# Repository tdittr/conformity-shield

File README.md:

# Conformity Shield

This is a design for a Arduino Uno R3 compatible shield, that connects an RP2354B to all IO pins. It is inteded to be used to test implementations of [`embedded-hal`](https://docs.rs/embedded-hal/).

**Warning:** rev1 of this board has known problems, do not produce boards from this yet, see the issue tracker for details!

## License

This project is licensed under the [CERN-OHL-P license](LICENSE), except for the contents of [`ProjectSpecific.pretty`](ProjectSpecific.pretty) and [`Project_Specific.kicad_sym`](Project_Specific.kicad_sym) which are partially copied from the [RP235xB example](https://datasheets.raspberrypi.com/rp2350/hardware-design-with-rp2350.pdf) by Raspberry Pi.

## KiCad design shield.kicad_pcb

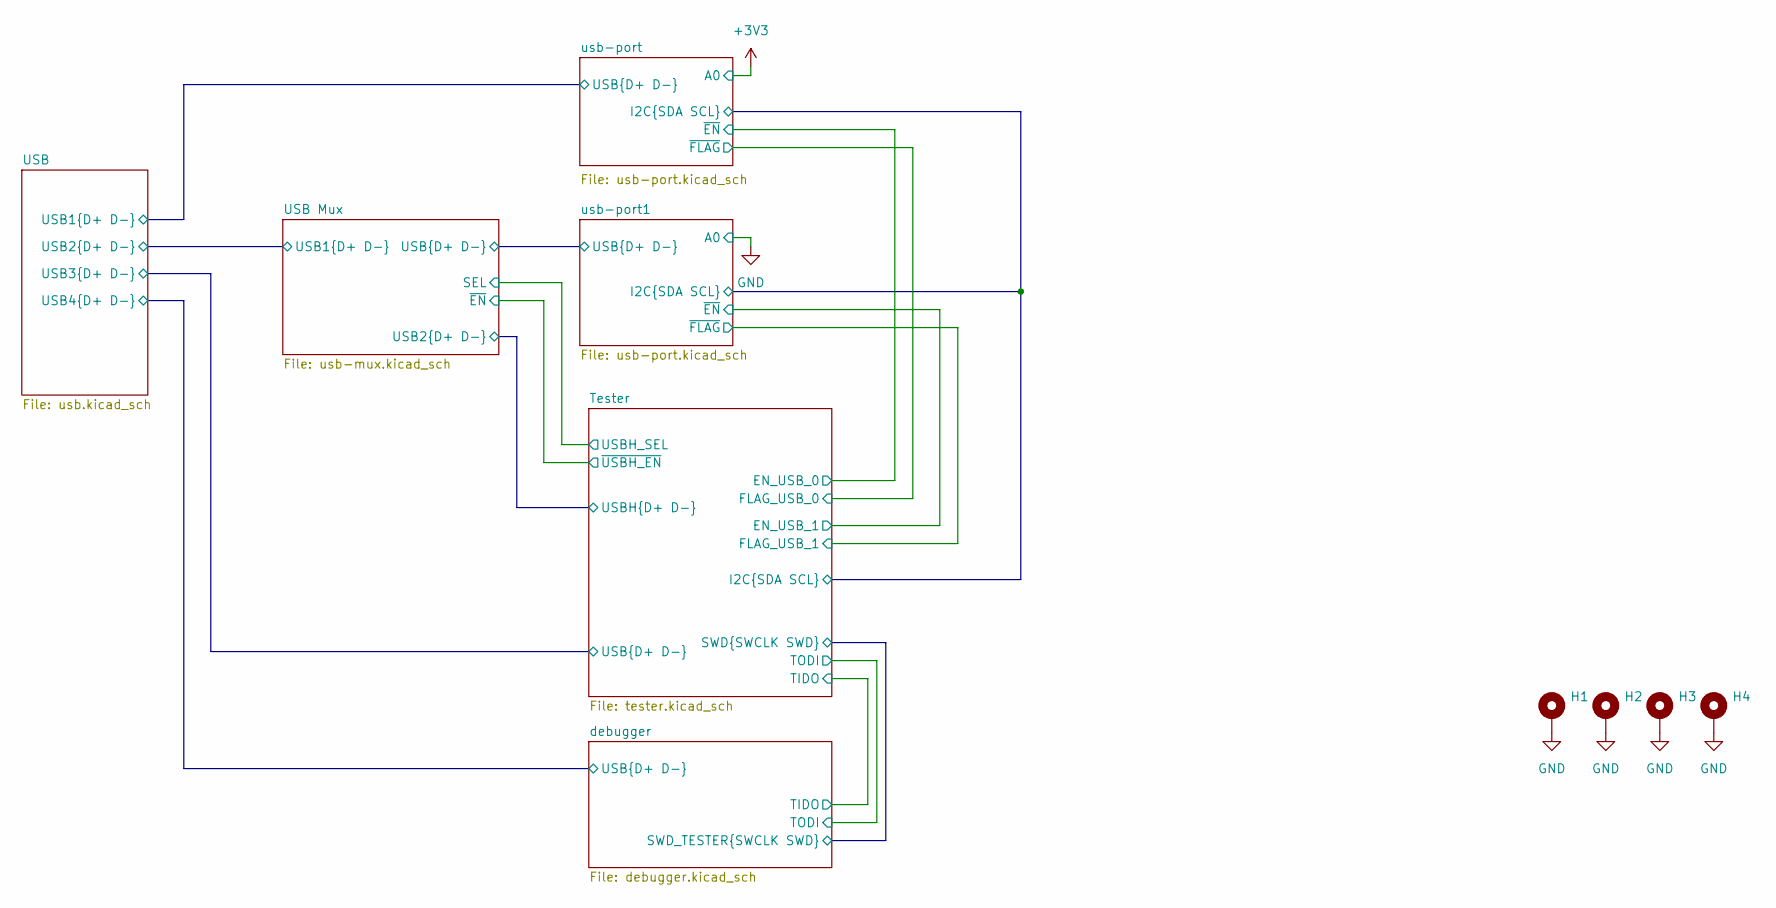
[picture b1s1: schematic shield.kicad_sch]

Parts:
H1, H2, H3, H4: MountingHole_Pad; MountingHole_2.5mm_Pad_Via

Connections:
GND: H1.1, H2.1, H3.1, H4.1; also elsewhere on the board

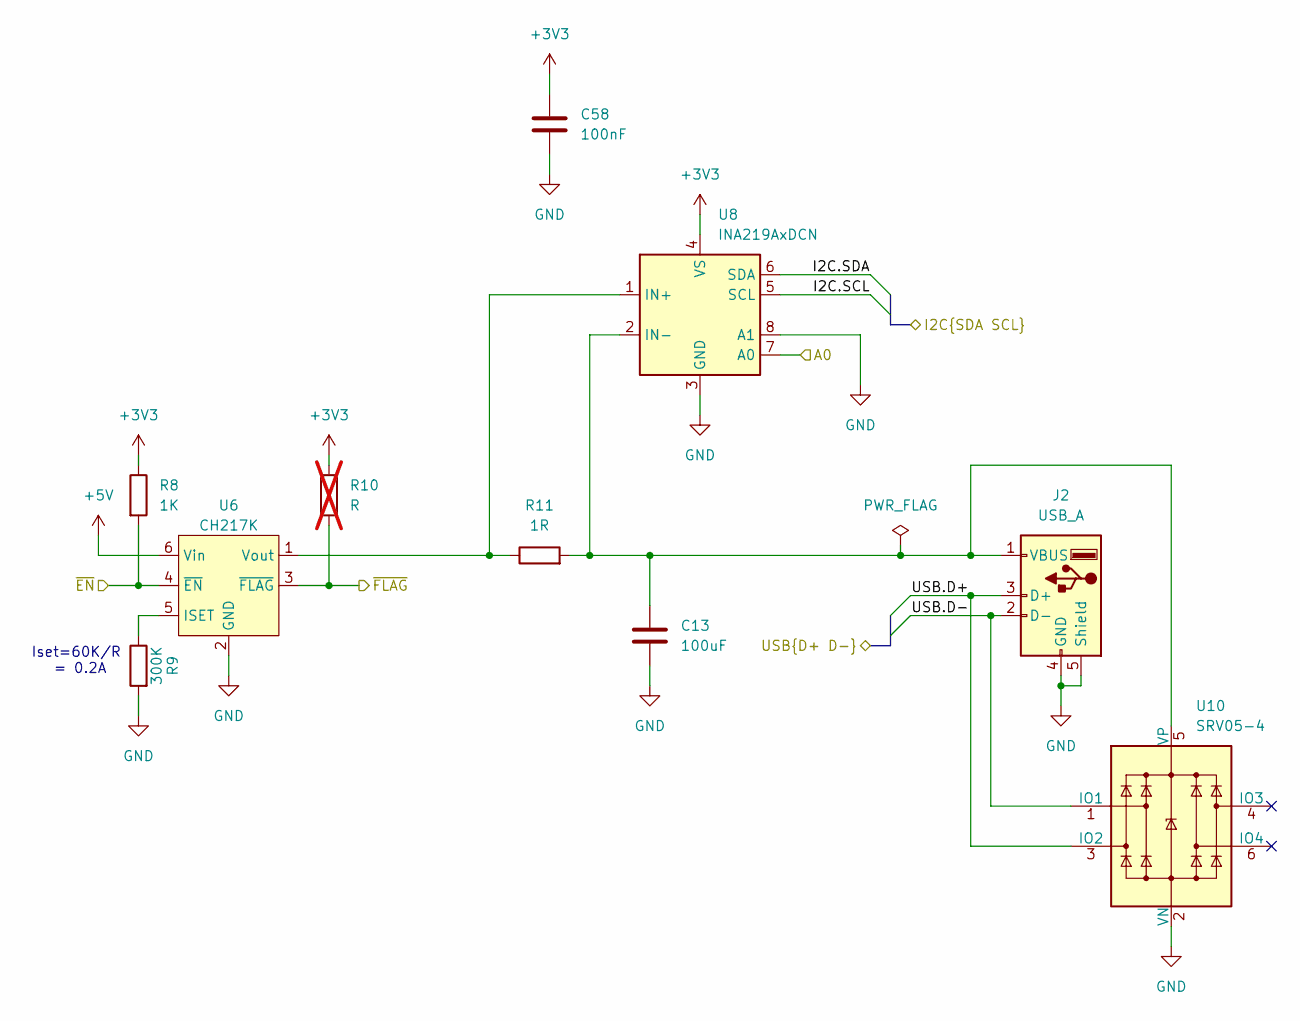
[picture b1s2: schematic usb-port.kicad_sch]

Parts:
C13: 100uF; C_1206_3216Metric; LCSC C15008
C58: 100nF; C_0402_1005Metric; LCSC C1525
J2: USB_A; USB_A_Receptacle_GCT_USB1046; LCSC C6307429
R8: 1K; R_0402_1005Metric; LCSC C11702
R9: 300K; R_0603_1608Metric; LCSC C23024
R10: R; R_0603_1608Metric_Pad0.98x0.95mm_HandSolder; not fitted
R11: 1R; R_0402_1005Metric; LCSC C25086
U6: CH217K; SOT-23-6; LCSC C7462749
U8: INA219AxDCN; SOT-23-8; LCSC C87469
U10: SRV05-4; SOT-23-6; LCSC C7420376

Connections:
+3V3: C58.1, R8.1, R10.1, U8.4 (VS), U8.7 (A0); also elsewhere on the board
+5V: U6.6 (Vin); also elsewhere on the board
/Tester/EN_USB_0: R8.2, U6.4 (~EN); also elsewhere on the board
/Tester/FLAG_USB_0: R10.2, U6.3 (~FLAG); also elsewhere on the board
/Tester/I2C.SCL: U8.5 (SCL); also elsewhere on the board
/Tester/I2C.SDA: U8.6 (SDA); also elsewhere on the board
/USB/USB1.D+: J2.3 (D+), U10.3 (IO2); also elsewhere on the board
/USB/USB1.D-: J2.2 (D-), U10.1 (IO1); also elsewhere on the board
GND: C13.2, C58.2, J2.4 (GND), J2.5 (Shield), R9.2, U6.2 (GND), U8.3 (GND), U8.8 (A1), U10.2 (VN); also elsewhere on the board
unnamed: C13.1, J2.1 (VBUS), R11.2, U8.2 (IN-), U10.5 (VP)
unnamed: R9.1, U6.5 (ISET)
unnamed: R11.1, U6.1 (Vout), U8.1 (IN+)

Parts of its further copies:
C52: 100uF; C_1206_3216Metric; LCSC C15008
C59: 100nF; C_0402_1005Metric; LCSC C1525
J3: USB_A; USB_A_Receptacle_GCT_USB1046; LCSC C6307429
R12: 1K; R_0402_1005Metric; LCSC C11702
R13: 300K; R_0603_1608Metric; LCSC C23024
R14: R; R_0603_1608Metric_Pad0.98x0.95mm_HandSolder; not fitted
R15: 1R; R_0402_1005Metric; LCSC C25086
U7: CH217K; SOT-23-6; LCSC C7462749
U9: INA219AxDCN; SOT-23-8; LCSC C87469
U11: SRV05-4; SOT-23-6; LCSC C7420376

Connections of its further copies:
+3V3: C59.1, R12.1, R14.1, U9.4 (VS); also elsewhere on the board
+5V: U7.6 (Vin); also elsewhere on the board
/Tester/EN_USB_1: R12.2, U7.4 (~EN); also elsewhere on the board
/Tester/FLAG_USB_1: R14.2, U7.3 (~FLAG); also elsewhere on the board
/Tester/I2C.SCL: U9.5 (SCL); also elsewhere on the board
/Tester/I2C.SDA: U9.6 (SDA); also elsewhere on the board
/USB Mux/USB.D+: J3.3 (D+), U11.3 (IO2); also elsewhere on the board
/USB Mux/USB.D-: J3.2 (D-), U11.1 (IO1); also elsewhere on the board
GND: C52.2, C59.2, J3.4 (GND), J3.5 (Shield), R13.2, U7.2 (GND), U9.3 (GND), U9.7 (A0), U9.8 (A1), U11.2 (VN); also elsewhere on the board
unnamed: C52.1, J3.1 (VBUS), R15.2, U9.2 (IN-), U11.5 (VP)
unnamed: R13.1, U7.5 (ISET)
unnamed: R15.1, U7.1 (Vout), U9.1 (IN+)

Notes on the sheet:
Iset=60K/R = 0.2A

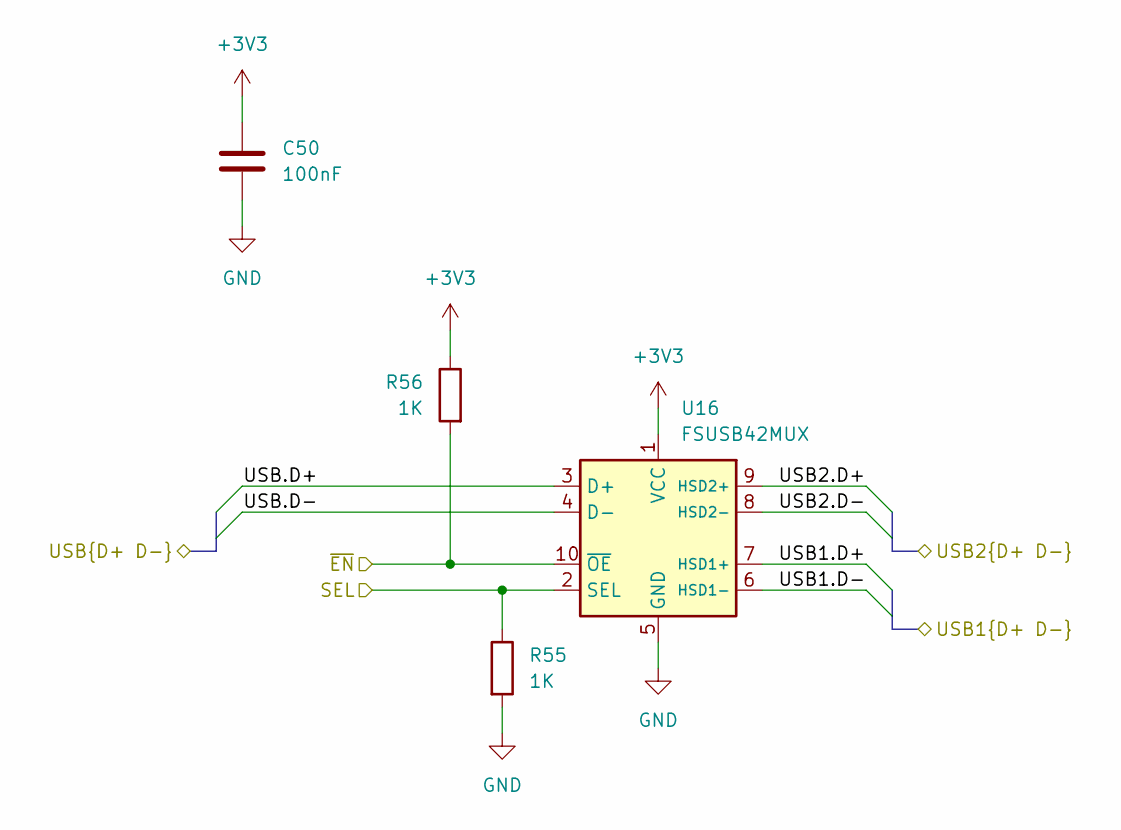
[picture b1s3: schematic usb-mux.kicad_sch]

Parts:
C50: 100nF; C_0402_1005Metric; LCSC C1525
R55, R56: 1K; R_0402_1005Metric; LCSC C11702
U16: FSUSB42MUX; MSOP-10_3x3mm_P0.5mm; LCSC C11355

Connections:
+3V3: C50.1, R56.1, U16.1 (VCC); also elsewhere on the board
/Tester/USBH.D+: U16.9 (HSD2+); also elsewhere on the board
/Tester/USBH.D-: U16.8 (HSD2-); also elsewhere on the board
/Tester/USBH_SEL: R55.1, U16.2 (SEL); also elsewhere on the board
/Tester/~USBH_EN: R56.2, U16.10 (~OE); also elsewhere on the board
/USB Mux/USB1.D+: U16.7 (HSD1+); also elsewhere on the board
/USB Mux/USB1.D-: U16.6 (HSD1-); also elsewhere on the board
/USB Mux/USB.D+: U16.3 (D+); also elsewhere on the board
/USB Mux/USB.D-: U16.4 (D-); also elsewhere on the board
GND: C50.2, R55.2, U16.5 (GND); also elsewhere on the board

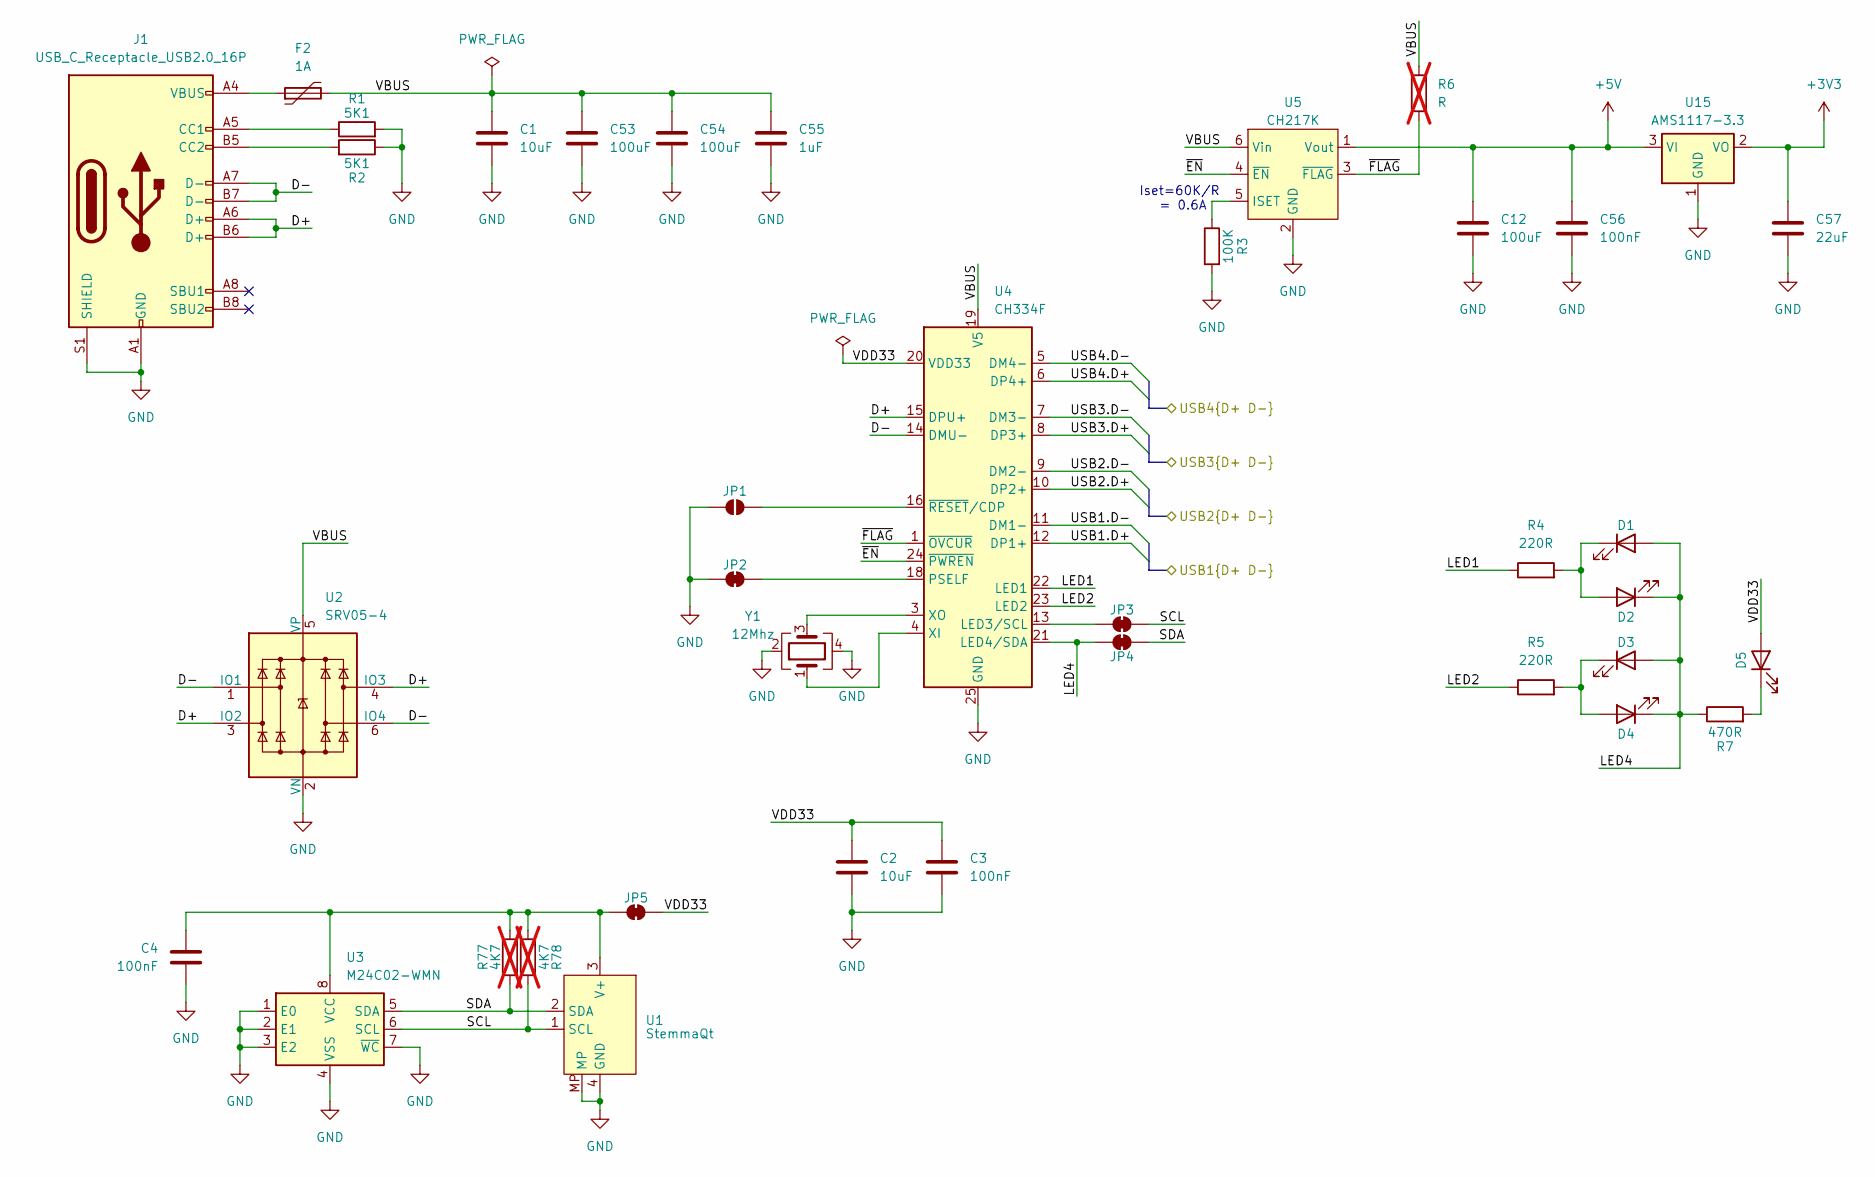
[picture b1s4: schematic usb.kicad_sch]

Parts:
C1, C2: 10uF; C_0402_1005Metric; LCSC C15525
C3, C4, C56: 100nF; C_0402_1005Metric; LCSC C1525
C12, C53, C54: 100uF; C_1206_3216Metric; LCSC C15008
C55: 1uF; C_0402_1005Metric; LCSC C52923
C57: 22uF; C_0805_2012Metric; LCSC C45783
D1, D2, D3, D4, D5: LED; LED_0805_2012Metric; LCSC C2297
F2: 1A; Fuse_1206_3216Metric_Pad1.42x1.75mm_HandSolder; LCSC C720075
J1: USB_C_Receptacle_USB2.0_16P; USB_C_Receptacle_G-Switch_GT-USB-7010ASV; LCSC C2988369
JP1: SolderJumper_2_Open; SolderJumper-2_P1.3mm_Open_RoundedPad1.0x1.5mm
JP2, JP3, JP4, JP5: SolderJumper_2_Bridged; SolderJumper-2_P1.3mm_Bridged_RoundedPad1.0x1.5mm
R1, R2: 5K1; R_0402_1005Metric; LCSC C25905
R3: 100K; R_0603_1608Metric; LCSC C23162
R4, R5: 220R; R_0402_1005Metric; LCSC C25091
R6: R; R_0603_1608Metric_Pad0.98x0.95mm_HandSolder; not fitted
R7: 470R; R_0402_1005Metric; LCSC C25117
R77, R78: 4K7; R_0402_1005Metric_Pad0.72x0.64mm_HandSolder; LCSC C25900; not fitted
U1: StemmaQt; JST_SH_SM04B-SRSS-TB_1x04-1MP_P1.00mm_Horizontal; LCSC C160404
U2: SRV05-4; SOT-23-6; LCSC C7420376
U3: M24C02-WMN; SOIC-8_3.9x4.9mm_P1.27mm; LCSC C7562
U4: CH334F; QFN-24-1EP_4x4mm_P0.5mm_EP2.7x2.7mm_ThermalVias; LCSC C5187527
U5: CH217K; SOT-23-6; LCSC C7462749
U15: AMS1117-3.3; SOT-223-3_TabPin2; LCSC C6186
Y1: 12Mhz; Crystal_SMD_3225-4Pin_3.2x2.5mm; LCSC C9002

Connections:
+3V3: C57.1, U15.2 (VO); also elsewhere on the board
+5V: C12.1, C56.1, U5.1 (Vout), U15.3 (VI); also elsewhere on the board
/Tester/USB.D+: U4.8 (DP3+); also elsewhere on the board
/Tester/USB.D-: U4.7 (DM3-); also elsewhere on the board
/USB Mux/USB1.D+: U4.10 (DP2+); also elsewhere on the board
/USB Mux/USB1.D-: U4.9 (DM2-); also elsewhere on the board
/USB/D+: J1.A6 (D+), J1.B6 (D+), U2.3 (IO2), U2.4 (IO3), U4.15 (DPU+)
/USB/D-: J1.A7 (D-), J1.B7 (D-), U2.1 (IO1), U2.6 (IO4), U4.14 (DMU-)
/USB/LED1: R4.1, U4.22 (LED1)
/USB/LED2: R5.1, U4.23 (LED2)
/USB/LED4: D1.2 (A), D2.1 (K), D3.2 (A), D4.1 (K), JP4.1 (A), R7.1, U4.21 (LED4/SDA)
/USB/SCL: JP3.2 (B), R78.1, U1.1 (SCL), U3.6 (SCL)
/USB/SDA: JP4.2 (B), R77.1, U1.2 (SDA), U3.5 (SDA)
/USB/USB1.D+: U4.12 (DP1+); also elsewhere on the board
/USB/USB1.D-: U4.11 (DM1-); also elsewhere on the board
/USB/USB4.D+: U4.6 (DP4+); also elsewhere on the board
/USB/USB4.D-: U4.5 (DM4-); also elsewhere on the board
/USB/VBUS: C1.1, C53.1, C54.1, C55.1, F2.2, R6.1, U2.5 (VP), U4.19 (V5), U5.6 (Vin)
/USB/VDD33: C2.1, C3.1, D5.2 (A), JP5.2 (B), U4.20 (VDD33)
/USB/~EN: U4.24 (~PWREN), U5.4 (~EN)
/USB/~FLAG: R6.2, U4.1 (~OVCUR), U5.3 (~FLAG)
GND: C1.2, C2.2, C3.2, C4.2, C12.2, C53.2, C54.2, C55.2, C56.2, C57.2, J1.A1 (GND), J1.A12 (GND), J1.B1 (GND), J1.B12 (GND), J1.S1 (SHIELD), JP1.1 (A), JP2.1 (A), R1.2, R2.1, R3.2, U1.4 (GND), U1.MP, U2.2 (VN), U3.1 (E0), U3.2 (E1), U3.3 (E2), U3.4 (VSS), U3.7 (~WC), U4.25 (GND), U5.2 (GND), U15.1 (GND), Y1.2, Y1.4; also elsewhere on the board
unnamed: D1.1 (K), D2.2 (A), R4.2
unnamed: D3.1 (K), D4.2 (A), R5.2
unnamed: D5.1 (K), R7.2
unnamed: F2.1, J1.A4 (VBUS), J1.A9 (VBUS), J1.B4 (VBUS), J1.B9 (VBUS)
unnamed: J1.A5 (CC1), R1.1
unnamed: J1.B5 (CC2), R2.2
unnamed: JP1.2 (B), U4.16 (~RESET/CDP)
unnamed: JP2.2 (B), U4.18 (PSELF)
unnamed: JP3.1 (A), U4.13 (LED3/SCL)
unnamed: C4.1, JP5.1 (A), R77.2, R78.2, U1.3 (V+), U3.8 (VCC)
unnamed: U4.4 (XI), Y1.1
unnamed: U4.3 (XO), Y1.3
unnamed: R3.1, U5.5 (ISET)

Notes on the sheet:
Iset=60K/R = 0.6A

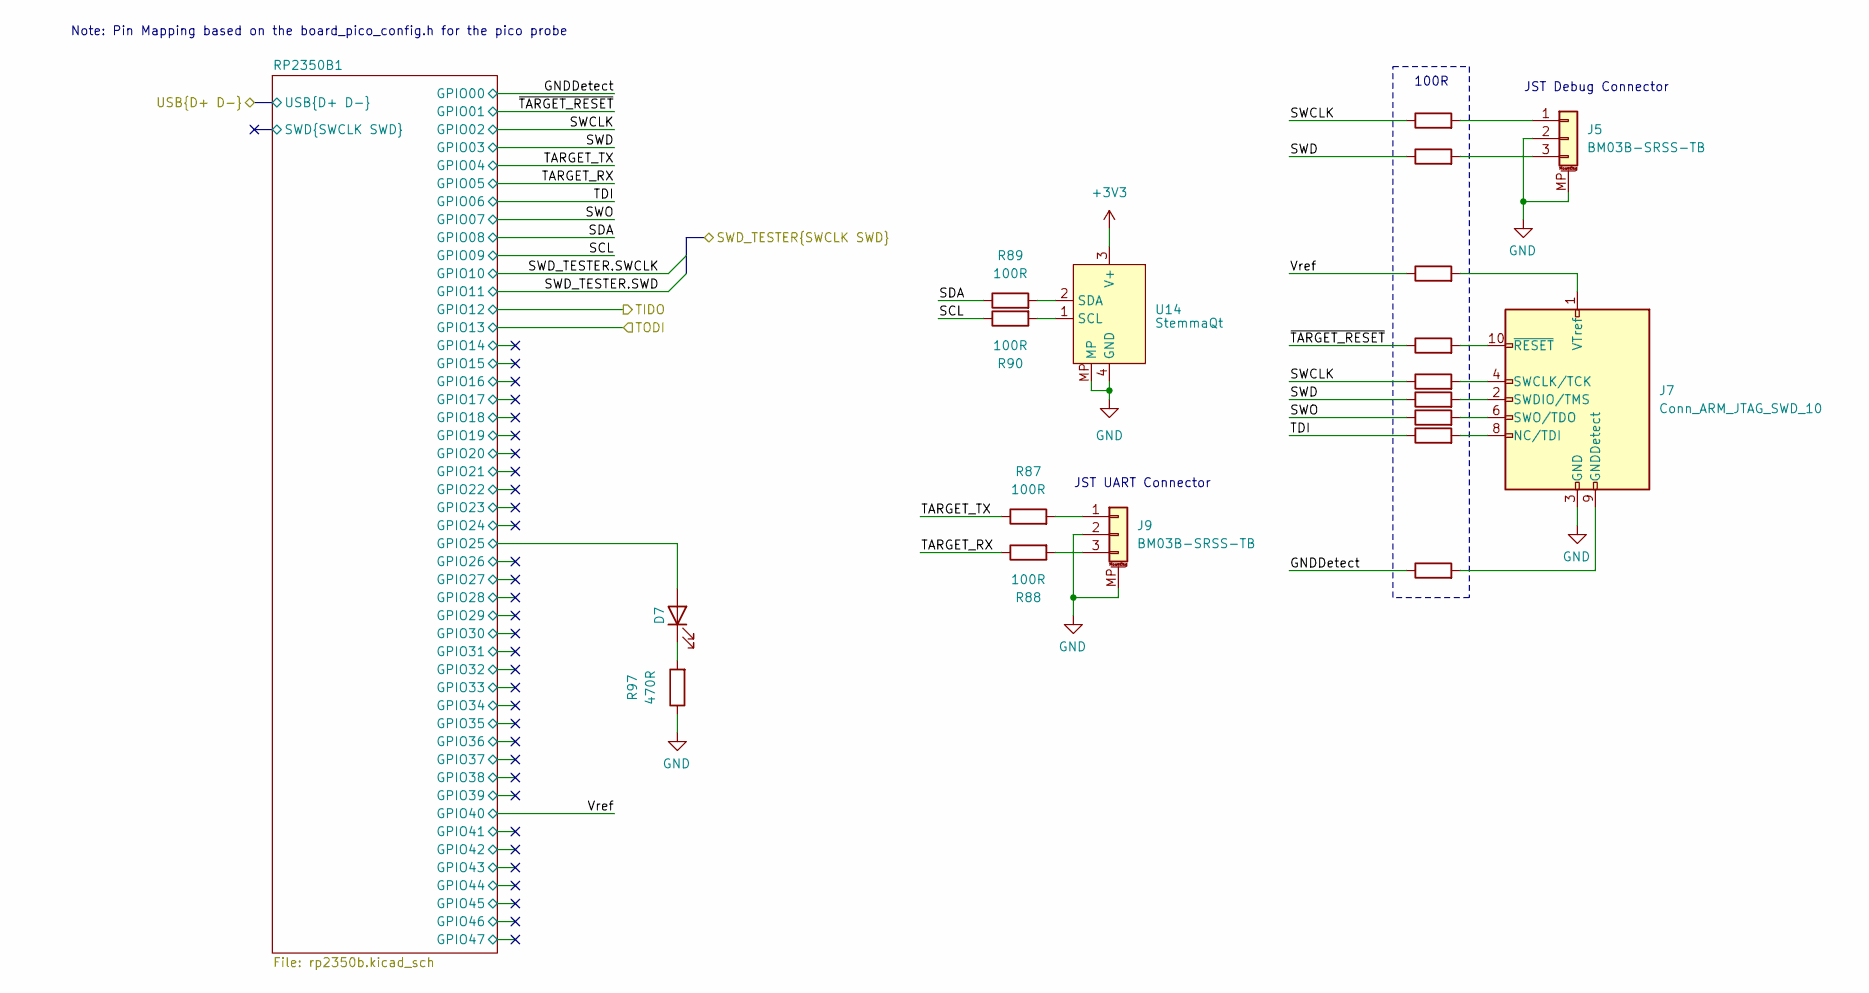
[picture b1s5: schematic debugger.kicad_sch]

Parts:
D7: LED; LED_0805_2012Metric; LCSC C2297
J5, J9: BM03B-SRSS-TB; JST_SH_BM03B-SRSS-TB_1x03-1MP_P1.00mm_Vertical; LCSC C160389
J7: Conn_ARM_JTAG_SWD_10; PinHeader_2x05_P1.27mm_Vertical_SMD_IDC; LCSC C42372555
R69, R70, R71, R72, R73, R74, R81, R85, R86, R87, R88, R89, R90: 100R; R_0402_1005Metric_Pad0.72x0.64mm_HandSolder; LCSC C25076
R97: 470R; R_0402_1005Metric_Pad0.72x0.64mm_HandSolder; LCSC C25117
U14: StemmaQt; JST_SH_SM04B-SRSS-TB_1x04-1MP_P1.00mm_Horizontal; LCSC C160404

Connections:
+3V3: U14.3 (V+); also elsewhere on the board
/debugger/GNDDetect: R81.1; also elsewhere on the board
/debugger/RP2350B1/GPIO25: D7.2 (A); also elsewhere on the board
/debugger/SCL: R90.1; also elsewhere on the board
/debugger/SDA: R89.1; also elsewhere on the board
/debugger/SWCLK: R71.1, R85.1; also elsewhere on the board
/debugger/SWD: R72.1, R86.1; also elsewhere on the board
/debugger/SWO: R73.1; also elsewhere on the board
/debugger/TARGET_RX: R88.1; also elsewhere on the board
/debugger/TARGET_TX: R87.1; also elsewhere on the board
/debugger/TDI: R74.1; also elsewhere on the board
/debugger/Vref: R69.1; also elsewhere on the board
/debugger/~TARGET_RESET: R70.1; also elsewhere on the board
GND: J5.2, J5.MP (MountPin), J7.3 (GND), J7.5 (GND), J9.2, J9.MP (MountPin), R97.1, U14.4 (GND), U14.MP; also elsewhere on the board
unnamed: D7.1 (K), R97.2
unnamed: J5.1, R85.2
unnamed: J5.3, R86.2
unnamed: J7.9 (GNDDetect), R81.2
unnamed: J7.8 (NC/TDI), R74.2
unnamed: J7.4 (SWCLK/TCK), R71.2
unnamed: J7.2 (SWDIO/TMS), R72.2
unnamed: J7.6 (SWO/TDO), R73.2
unnamed: J7.1 (VTref), R69.2
unnamed: J7.10 (~RESET), R70.2
unnamed: J9.1, R87.2
unnamed: J9.3, R88.2
unnamed: R90.2, U14.1 (SCL)
unnamed: R89.2, U14.2 (SDA)

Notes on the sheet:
Note: Pin Mapping based on the board_pico_config.h for the pico probe
JST UART Connector
100R
JST Debug Connector

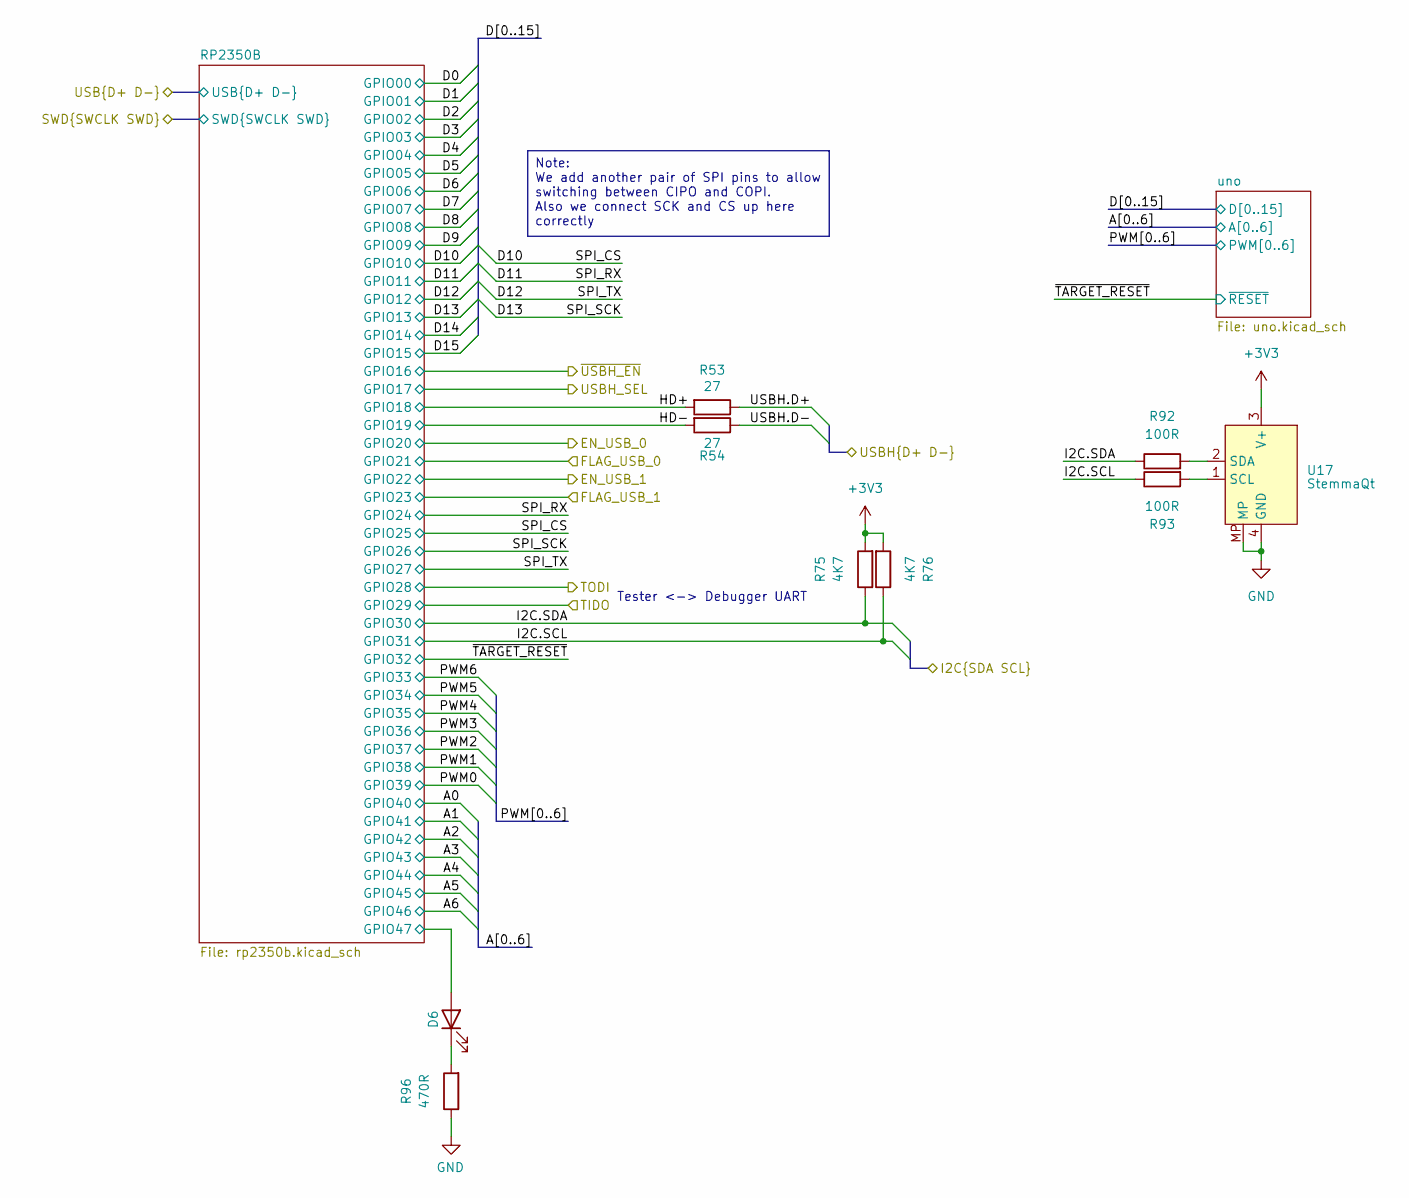
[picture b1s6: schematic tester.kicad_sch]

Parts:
D6: LED; LED_0805_2012Metric; LCSC C2297
R53, R54: 27; R_0402_1005Metric; LCSC C138021
R75, R76: 4K7; R_0402_1005Metric_Pad0.72x0.64mm_HandSolder; LCSC C25900
R92, R93: 100R; R_0402_1005Metric_Pad0.72x0.64mm_HandSolder; LCSC C25076
R96: 470R; R_0402_1005Metric_Pad0.72x0.64mm_HandSolder; LCSC C25117
U17: StemmaQt; JST_SH_SM04B-SRSS-TB_1x04-1MP_P1.00mm_Horizontal; LCSC C160404

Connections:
+3V3: R75.2, R76.2, U17.3 (V+); also elsewhere on the board
/Tester/HD+: R53.2; also elsewhere on the board
/Tester/HD-: R54.2; also elsewhere on the board
/Tester/I2C.SCL: R76.1, R93.1; also elsewhere on the board
/Tester/I2C.SDA: R75.1, R92.1; also elsewhere on the board
/Tester/RP2350B/GPIO47: D6.2 (A); also elsewhere on the board
/Tester/USBH.D+: R53.1; also elsewhere on the board
/Tester/USBH.D-: R54.1; also elsewhere on the board
GND: R96.1, U17.4 (GND), U17.MP; also elsewhere on the board
unnamed: D6.1 (K), R96.2
unnamed: R93.2, U17.1 (SCL)
unnamed: R92.2, U17.2 (SDA)

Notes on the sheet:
Tester <-> Debugger UART
Note: We add another pair of SPI pins to allow switching between CIPO and COPI. Also we connect SCK and CS up here correctly
